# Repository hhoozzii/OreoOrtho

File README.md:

# OreoOrtho
 practice Atmega32u2-AU with USB-C port, ESD protection diode, YS-SK6812MINI-E LEDS under each of the four switches.

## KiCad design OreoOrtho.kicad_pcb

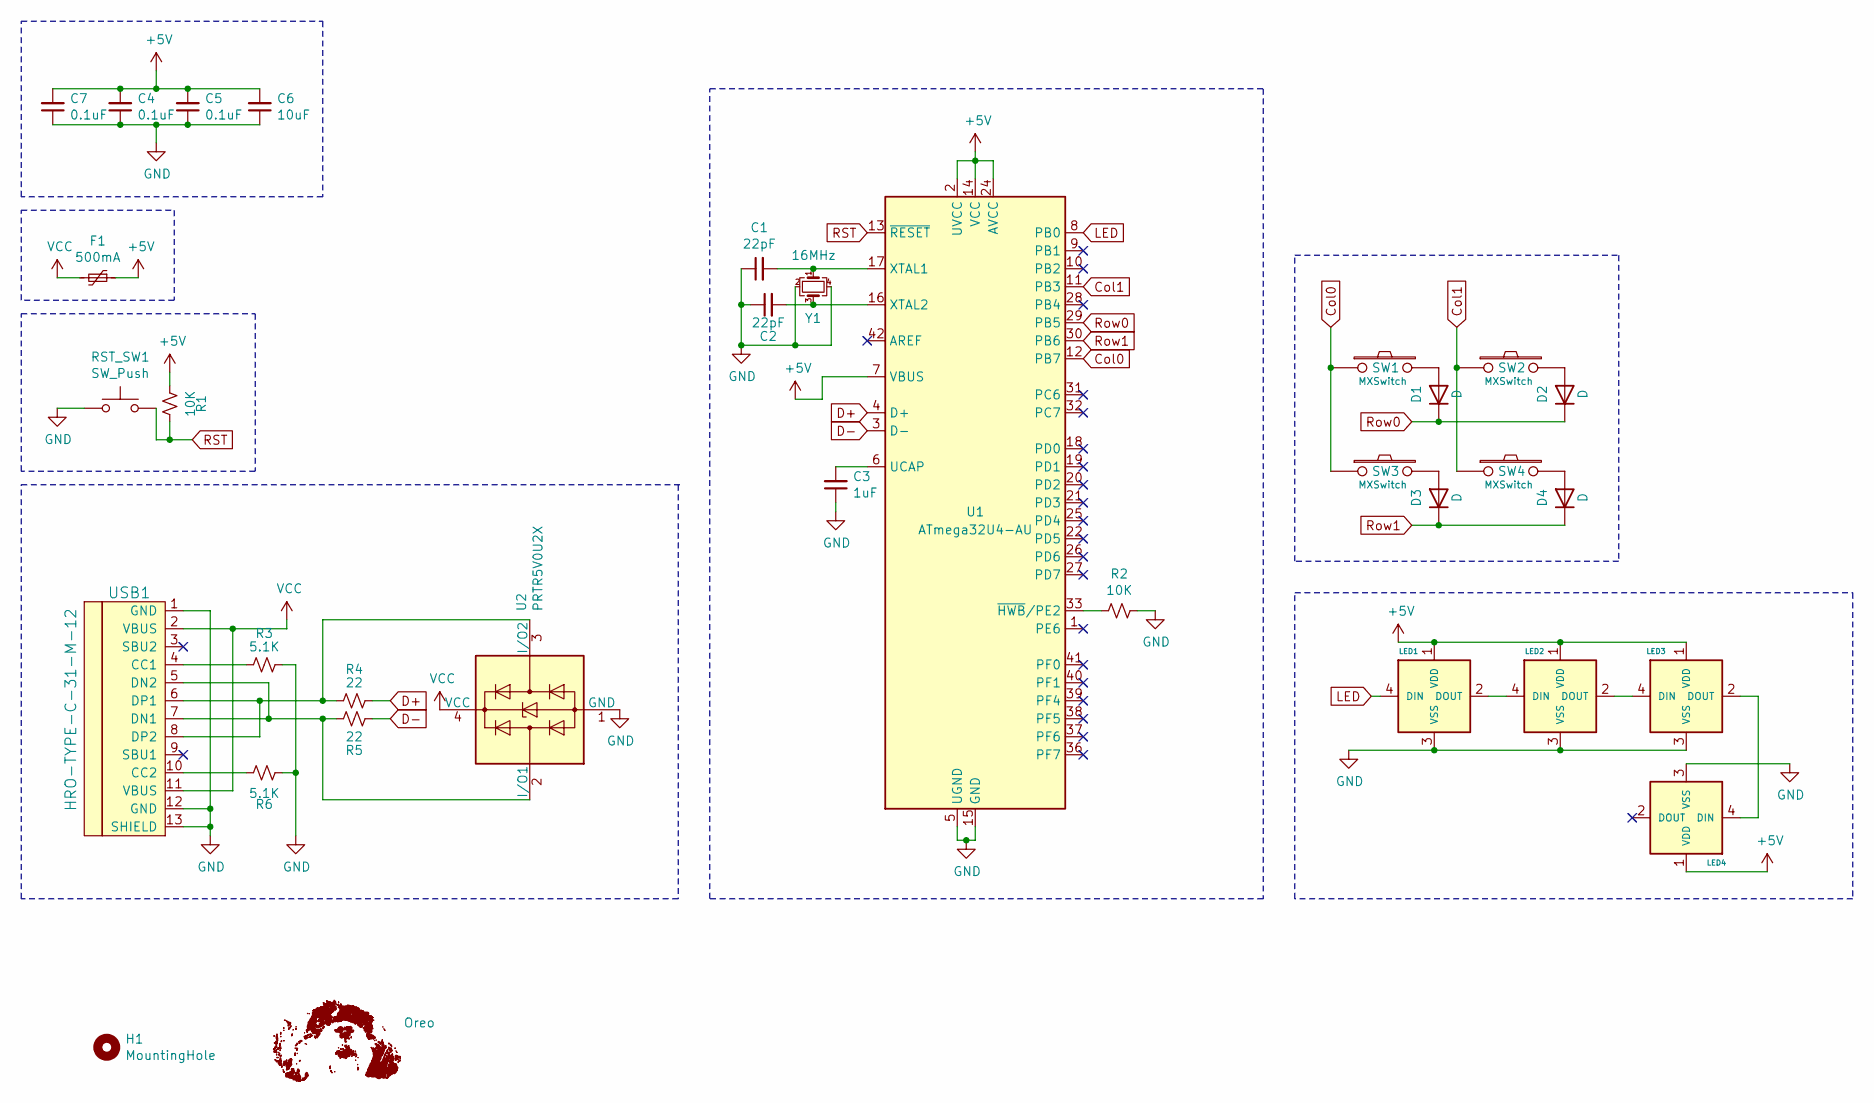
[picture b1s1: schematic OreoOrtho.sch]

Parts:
C1, C2: 22pF; C_0603_1608Metric
C3: 1uF; C_0603_1608Metric
C4, C5, C7: 0.1uF; C_0603_1608Metric
C6: 10uF; C_0603_1608Metric
D1, D2, D3, D4: D; D3_SMD_v2
F1: 500mA; Fuse_1206_3216Metric
G2: Oreo; bike
H1: MountingHole; HOLE
LED1, LED2, LED3, LED4: YS-SK6812MINI-E
R1, R2: 10K; R_0805_2012Metric
R3, R6: 5.1K; R_0805_2012Metric
R4, R5: 22; R_0805_2012Metric
RST_SW1: SW_Push; SKQG-1155865
SW1, SW2, SW3, SW4: MXSwitch; CherryMX_Hotswap_clear
U1: ATmega32U4-AU; TQFP-44_10x10mm_P0.8mm
U2: PRTR5V0U2X; SOT-143
USB1: HRO-TYPE-C-31-M-12
Y1: 16MHz; Crystal_SMD_3225-4Pin_3.2x2.5mm_HandSoldering

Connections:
+5V: C4.2, C5.2, C6.2, C7.2, F1.1, LED1.1 (VDD), LED2.1 (VDD), LED3.1 (VDD), LED4.1 (VDD), R1.2, U1.2 (UVCC), U1.7 (VBUS), U1.14 (VCC), U1.24 (AVCC), U1.34 (VCC), U1.44 (AVCC)
Col0: SW1.1, SW3.1, U1.12 (PB7)
Col1: SW2.1, SW4.1, U1.11 (PB3)
D+: R4.2, U1.4 (D+)
D-: R5.1, U1.3 (D-)
GND: C1.1, C2.1, C3.1, C4.1, C5.1, C6.1, C7.1, LED1.3 (VSS), LED2.3 (VSS), LED3.3 (VSS), LED4.3 (VSS), R2.1, R3.2, R6.2, RST_SW1.1, U1.5 (UGND), U1.15 (GND), U1.23 (GND), U1.35 (GND), U1.43 (GND), U2.1 (GND), USB1.1 (GND), USB1.12 (GND), USB1.13 (SHIELD), Y1.2, Y1.4
LED: LED1.4 (DIN), U1.8 (PB0)
unnamed: C1.2, U1.17 (XTAL1), Y1.1
unnamed: C2.2, U1.16 (XTAL2), Y1.3
unnamed: C3.2, U1.6 (UCAP)
unnamed: D1.2 (A), SW1.2
unnamed: D2.2 (A), SW2.2
unnamed: D3.2 (A), SW3.2
unnamed: D4.2 (A), SW4.2
unnamed: LED1.2 (DOUT), LED2.4 (DIN)
unnamed: LED2.2 (DOUT), LED3.4 (DIN)
unnamed: LED3.2 (DOUT), LED4.4 (DIN)
unnamed: R2.2, U1.33 (~HWB~/PE2)
unnamed: R3.1, USB1.4 (CC1)
unnamed: R4.1, U2.3 (I/O2), USB1.6 (DP1), USB1.8 (DP2)
unnamed: R5.2, U2.2 (I/O1), USB1.5 (DN2), USB1.7 (DN1)
unnamed: R6.1, USB1.10 (CC2)
RST: R1.1, RST_SW1.2, U1.13 (~RESET)
Row0: D1.1 (K), D2.1 (K), U1.29 (PB5)
Row1: D3.1 (K), D4.1 (K), U1.30 (PB6)
VCC: F1.2, U2.4 (VCC), USB1.2 (VBUS), USB1.11 (VBUS)

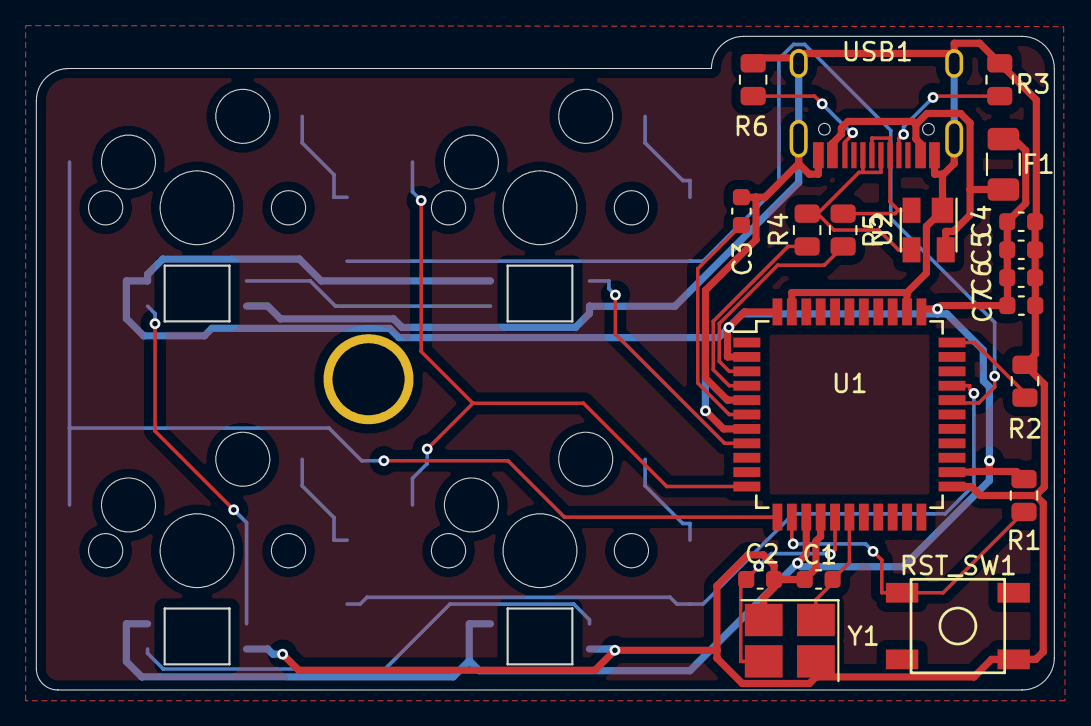
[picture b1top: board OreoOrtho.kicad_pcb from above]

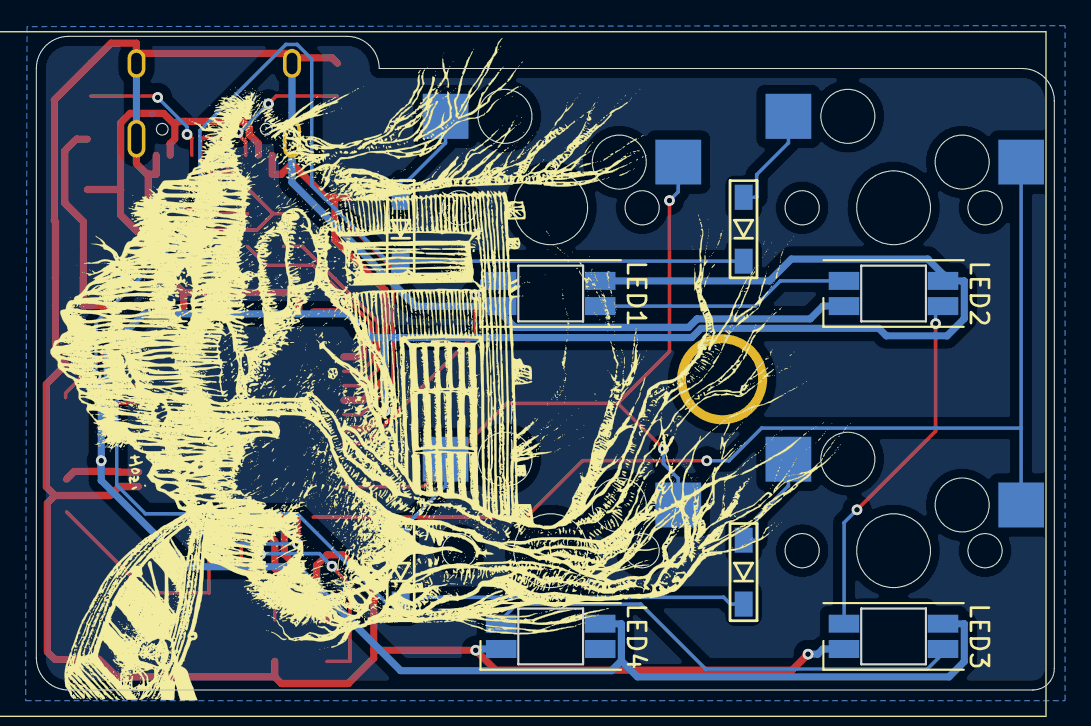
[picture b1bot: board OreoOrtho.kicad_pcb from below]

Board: 2 copper layers, 56.5 x 36.2 mm, 33 parts (9 on the bottom side), 26 nets.

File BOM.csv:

"Id";"Designator";"Package";"Quantity";"Designation";"Supplier and ref";
1;"U1";"TQFP-44_10x10mm_P0.8mm";1;"ATmega32U4-AU";;;
2;"C7,C5,C4";"C_0603_1608Metric";3;"0.1uF";;;
3;"USB1";"HRO-TYPE-C-31-M-12";1;"HRO-TYPE-C-31-M-12";;;
4;"SW4,SW3,SW2,SW1";"CherryMX_Hotswap_clear";4;"MXSwitch";;;
5;"H1";"HOLE";1;"MountingHole";;;
6;"Y1";"Crystal_SMD_3225-4Pin_3.2x2.5mm_HandSoldering";1;"16MHz";;;
7;"U2";"SOT-143";1;"PRTR5V0U2X";;;
8;"RST_SW1";"SKQG-1155865";1;"SW_Push";;;
9;"R6,R3";"R_0805_2012Metric";2;"5.1K";;;
10;"R5,R4";"R_0805_2012Metric";2;"22";;;
11;"R2,R1";"R_0805_2012Metric";2;"10K";;;
12;"LED4,LED3,LED2,LED1";"YS-SK6812MINI-E";4;"YS-SK6812MINI-E";;;
13;"F1";"Fuse_1206_3216Metric";1;"500mA";;;
14;"D4,D3,D2,D1";"D3_SMD_v2";4;"D";;;
15;"C6";"C_0603_1608Metric";1;"10uF";;;
16;"C3";"C_0603_1608Metric";1;"1uF";;;
17;"C2,C1";"C_0603_1608Metric";2;"22pF";;;

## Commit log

2020-10-15 start project
    setup kicad files
2020-10-15 add footprints
2020-10-16 more updates
2020-10-16 new mcu, fuse, etc
2020-10-17 changed mcu, usb
2020-10-17 made gerbers
2020-10-17 route ver1
2020-10-18 reroute
2020-10-27 minor file changes
2020-11-05 plates added
